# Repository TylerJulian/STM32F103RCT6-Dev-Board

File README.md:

# STM32F103RCT6 Developement board

A stm32f103RCT6 Breakout board for Sooner Competitive Robotics and Personal use.

Contains PORTs for CAN-Bus protocol and a 6 pin molex power and signal connection.

## Major Components

1x [STM32f103RCT6 microcontroller](https://www.mouser.com/ProductDetail/STMicroelectronics/STM32F103RCT6?qs=%252BB84zevwoRA6TYzZIgOIoA%3D%3D)

1x [SN65HVD230QDR CAN transceiver](https://www.mouser.com/ProductDetail/Texas-Instruments/SN65HVD230QDR?qs=QViXGNcIEAvSeznLG41lqg%3D%3D)

1x [Molex Connector](https://www.molex.com/molex/products/part-detail/pcb_headers/0430450612)

## Minor Components

See bill of materials

## Designers

- Tyler Julian - Designer - [TylerJulian](https://github.com/tylerjulian)

## Built With

- Kicad and Altium- Schematic designed in Kicad then imported to Altium  

## Errata
* tbd

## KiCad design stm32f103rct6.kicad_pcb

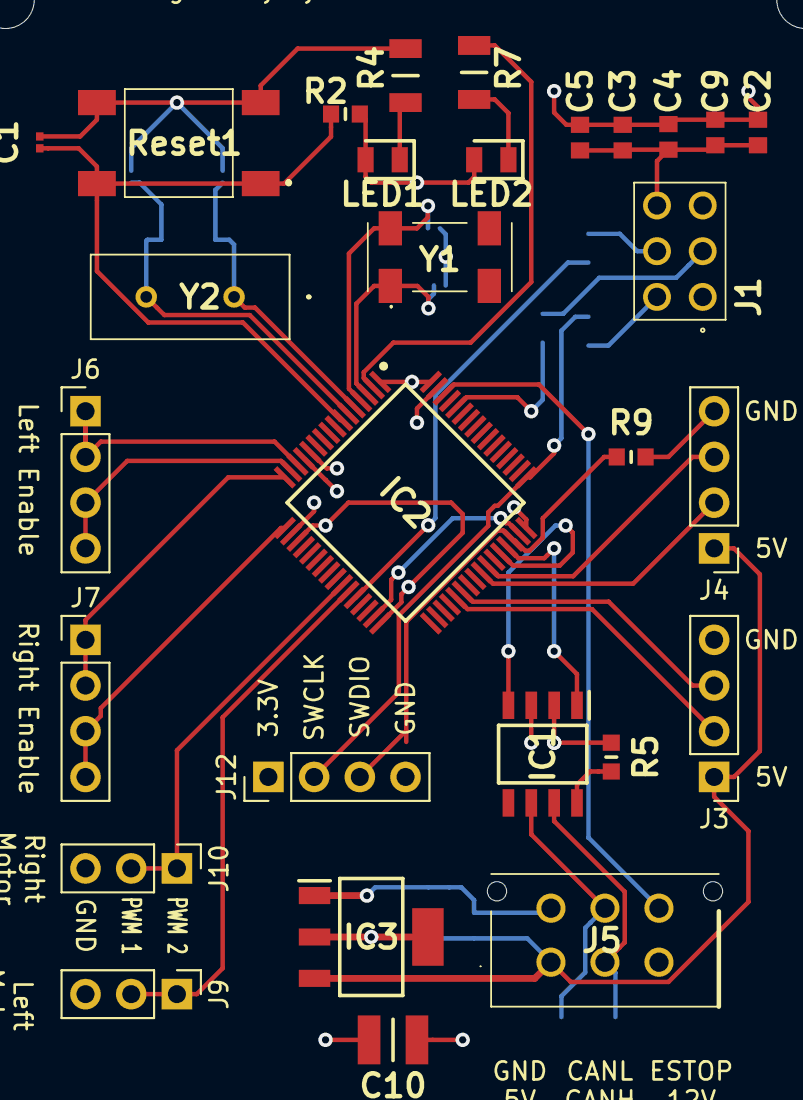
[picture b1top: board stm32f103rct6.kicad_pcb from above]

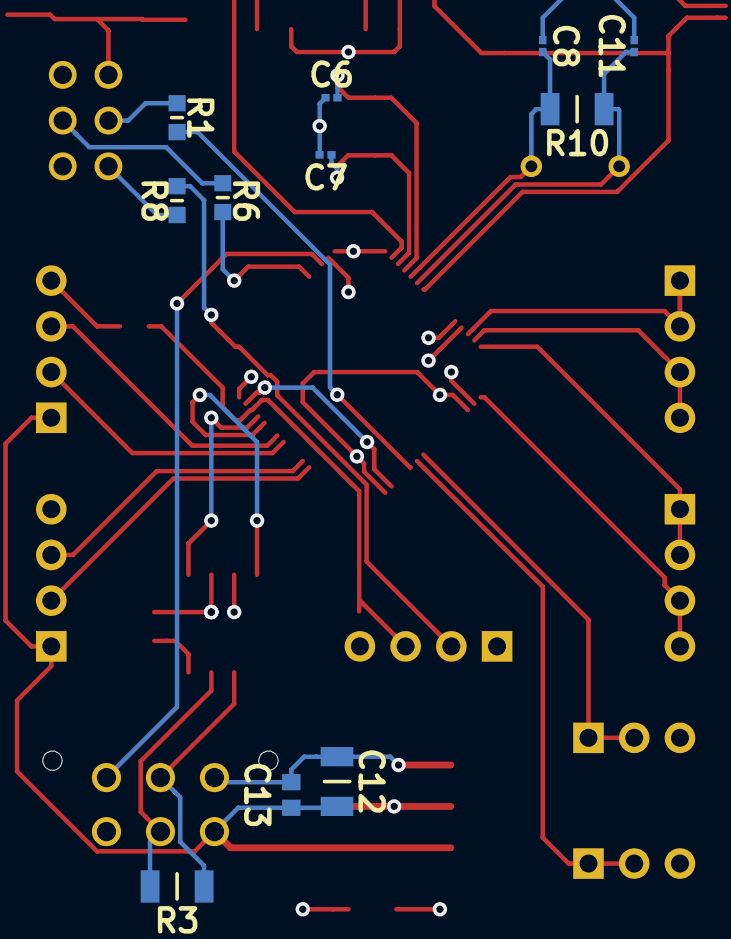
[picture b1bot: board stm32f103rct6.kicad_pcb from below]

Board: 4 copper layers, 40 parts (11 on the bottom side), 33 nets.

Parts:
C1: 1uF; CAPC0603X33N
C2, C3, C4, C5, C9, C13: 100nf; CAPC1608X100N
C6, C7: 8PF; CAPC0603X33N
C8, C11: 20pf; CAPC0603X33N
C10: 330uF; CAPC3225X270N
C12: 100uF; CAPC3216X180N
IC1: SN65HVD230QDR; SOIC127P600X175-8N
IC2: STM32F103RCT6; QFP50P1200X1200X160-64N
IC3: REG1117-3.3; SOT230P700X180-4N
J1: Boot Pins; TSW-103-XX-YY-D
J3: Righ Encoder; PinHeader_1x04_P2.54mm_Vertical
J4: Left Encoder; PinHeader_1x04_P2.54mm_Vertical
J5: CAN Molex; 430450612
J6: Left Enable; PinHeader_1x04_P2.54mm_Vertical
J7: Right Enable; PinHeader_1x04_P2.54mm_Vertical
J9: Right Motor PWM; PinHeader_1x03_P2.54mm_Vertical
J10: Left Motor PWM; PinHeader_1x03_P2.54mm_Vertical
J12: SWD; PinHeader_1x04_P2.54mm_Vertical
LED1: Power Indicator LED; LEDC2012X90N
LED2: LG_R971-KN-1; LEDC2012X80N
R1, R6: 100k; RESC1608X55N
R2, R5, R8, R9: 10k; RESC1608X55N
R3: 120; RESC3216X60N
R4, R7: 510; RESC3216X60N
R10: 1M; RESC3216X60N
Reset1: Reset; LL3301NF065QG
Y1: 32.768KHZ; ABS2532000KHZT
Y2: 8Mhz; LFXTAL057135Bulk

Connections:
5V: C12.1, C13.2, IC3.3, J3.1, J4.1, J5.3
BOOT0: IC2.60, R6.2
BOOT1: IC2.28, R1.1
CANH: IC1.7, J5.2, R3.1
CANL: IC1.6, J5.5, R3.2
CAN_RX: IC1.4, IC2.44
CAN_TX: IC1.1, IC2.45
ESTOP_SIGNAL: IC2.62, J5.4
GND: C1.2, C2.2, C3.2, C4.2, C5.2, C6.1, C7.2, C8.1, C9.2, C10.1, C11.2, C12.2, C13.1, IC1.2, IC2.12, IC2.18, IC2.31, IC2.47, IC2.63, IC3.1, J1.5, J1.6, J3.4, J4.4, J5.6, J9.3, J10.3, J12.4, R4.2, R5.2, R9.2, Reset1.3, Reset1.4
unnamed: IC1.8, R5.1
unnamed: J1.3, R6.1
unnamed: J1.4, R1.2
unnamed: LED1.1, R4.1
unnamed: LED2.1, R7.1
OSCIN: C8.2, IC2.5, R10.1, Y2.1
OSCOUT: C11.1, IC2.6, R10.2, Y2.2
PA0: IC2.14, J6.1, J6.2
PA1: IC2.15, J6.3, J6.4
PA2: IC2.16, J7.1, J7.2
PA3: IC2.17, J7.3, J7.4
PA8: IC2.41, J4.2
PA9: IC2.42, J4.3
PA13: IC2.46, J12.3, R9.1
PA14: IC2.49, J12.2, R8.2
PB0: IC2.26, J10.1, J10.2
PB1: IC2.27, J9.1, J9.2
PC6: IC2.37, J3.2
PC7: IC2.38, J3.3
PC13: IC2.2, R7.2
PC14: C7.1, IC2.3, Y1.1
PC15: C6.2, IC2.4, Y1.4
RESET: C1.1, IC2.7, R2.2, Reset1.1, Reset1.2
VCC: C2.1, C3.1, C4.1, C5.1, C9.1, C10.2, IC1.3, IC2.1, IC2.13, IC2.19, IC2.32, IC2.48, IC2.64, IC3.2, IC3.4, J1.1, J1.2, J12.1, LED1.2, LED2.2, R2.1, R8.1

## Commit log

2020-07-13 Initial version 1 of the dev board.
    Might need to reorganize the pinout headers.
2020-07-13 Annotate V1 of schematic
2020-07-14 Version 2 of the schematic
    Added JST connections for Enable, PWM, and Power
2020-07-21 Add files via upload
    Upload altium Schematic
2020-07-21 New pcb schematic
2020-07-21 Add Bill of Materials
2020-07-21 add PCB screenshot
2020-07-21 Version of the board that I ordered
2020-07-29 upload soldered board
